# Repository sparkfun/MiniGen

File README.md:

SparkFun MiniGen - Pro Mini Signal Generator Shield
===================================================

[  
*MiniGen Signal Generator (BOB-11420)*](https://www.sparkfun.com/products/11420)

The [MiniGen](https://www.sparkfun.com/products/11420) designed to be used
either as a stand-alone board or as a shield that can be placed on top of an
Arduino Pro Mini. It's capable of generating sine, square or triangle waves at
up to 3MHz, and approximately 1Vp-p. The output is at a DC offset of Vcc/2.
Neither the offset nor the amplitude can be varied.

The MiniGen can be powered by any voltage from 2.3V to 5.5V, so it can be used
with either a 3.3V or 5V Pro Mini without any voltage regulation or signal level
shifting needed.

Repository Contents
-------------------
* **/Hardware** - Eagle design files (.brd, .sch)
* **/Libraries** - Libraries for use with the <PRODUCT NAME>
* **/Production** - Production panel files (.brd)

Documentation
--------------
* **[Library](https://github.com/sparkfun/SparkFun_MiniGen_Arduino_Library)** -  Arduinolibrary for the MiniGen.
* **[Hookup Guide](https://learn.sparkfun.com/tutorials/minigen-hookup-guide)** - Basic hookup guide for the MiniGen.
* **[SparkFun Fritzing repo](https://github.com/sparkfun/Fritzing_Parts)** - Fritzing diagrams for SparkFun products.
* **[SparkFun 3D Model repo](https://github.com/sparkfun/3D_Models)** - 3D models of SparkFun products. 

License Information
-------------------
This product is _**open source**_! 

The **hardware** is released under [Creative Commons ShareAlike 4.0 International](https://creativecommons.org/licenses/by-sa/4.0/).

The **code** is beerware; if you see me (or any other SparkFun employee) at the local, and you've found our code helpful, please buy us a round!

Please use, reuse, and modify these files as you see fit. Please maintain attribution to SparkFun Electronics and release anything derivative under the same license.

Distributed as-is; no warranty is given.

- Your friends at SparkFun.

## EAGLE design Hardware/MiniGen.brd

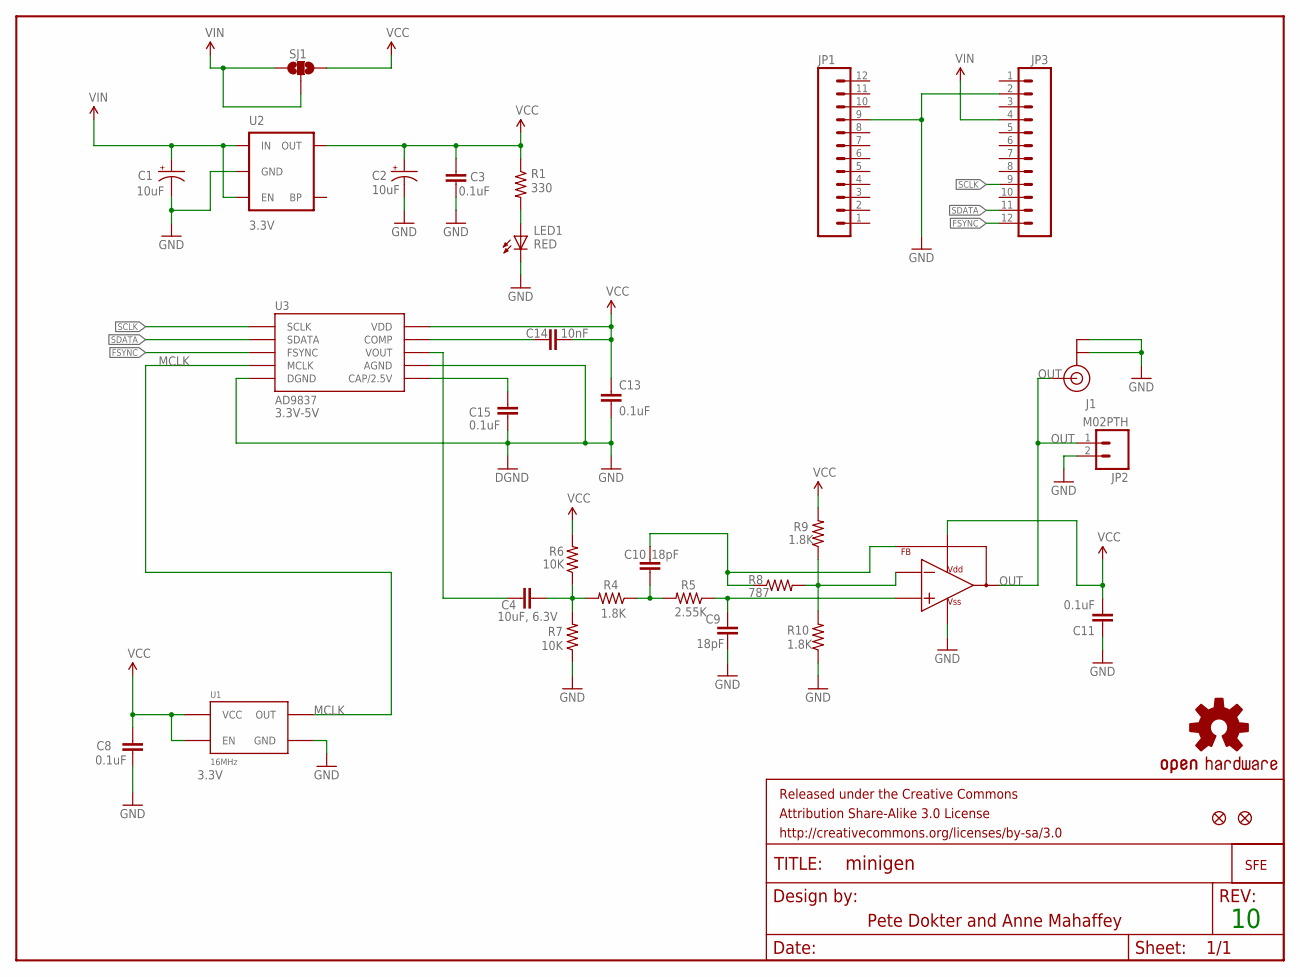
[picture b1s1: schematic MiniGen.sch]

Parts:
C1, C2: 10uF; EIA3528
C3, C8, C11, C13, C15: 0.1uF; 0603-CAP
C4: 10uF, 6.3V; 0603-CAP
C9, C10: 18pF; 0603-CAP
C14: 10nF; 0603-CAP
FID1, FID2: FIDUCIAL1X2; FIDUCIAL-1X2
FRAME1: FRAME-LETTER; CREATIVE_COMMONS
J1: U.FL
JP1, JP3: M12PTH; 1X12
JP2: M02PTH; 1X02
JP4: LOGO-SFENEW; SFE-NEW-WEBLOGO
LED1: RED; LED-0603
R1: 330; 0603-RES
R4, R9, R10: 1.8K; 0603-RES
R5: 2.55K; 0603-RES
R6, R7: 10K; 0603-RES
R8: 787; 0603-RES
SJ1: SOLDERJUMPER_2WAYT; SJ_2
U1: 16MHz; CRYSTAL-SMD-7X5
U2: 3.3V; SOT23-5
U3: AD9837
U4: ADC8045; SO08
U$2: OSHW-LOGOS; OSHW-LOGO-S

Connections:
FSYNC: JP3.12, U3.P$8 (FSYNC)
GND: C1.C (-), C2.C (-), C3.2, C8.2, C9.1, C11.1, C13.2, C15.2, J1.P$1 (GND), J1.P$2 (GND), JP1.9, JP2.2, JP3.2, LED1.C, R7.1, R10.1, U1.P$2 (GND), U2.2 (GND), U3.P$0 (DGND), U3.P$4 (DGND), U3.P$9 (AGND), U4.4 (VSS)
MCLK: U1.P$3 (OUT), U3.P$5 (MCLK)
unnamed: LED1.A, R1.2
unnamed: C9.2, R5.1, U4.3 (IN+)
unnamed: C10.1, R4.1, R5.2
unnamed: C10.2, R8.1, U4.1 (FB)
unnamed: C15.1, U3.P$3 (CAP/2.5V)
unnamed: R8.2, R9.1, R10.2, U4.2 (IN-)
unnamed: C4.2, R4.2, R6.1, R7.2
unnamed: C4.1, U3.P$10 (VOUT)
unnamed: C14.1, U3.P$1 (COMP)
OUT: J1.P$3 (SIGNAL), JP2.1, U4.6 (OUT)
SCLK: JP3.9, U3.P$7 (SCLK)
SDATA: JP3.11, U3.P$6 (SDATA)
VCC: C2.A (+), C3.1, C8.1, C11.2, C13.1, C14.2, R1.1, R6.2, R9.2, SJ1.3, U1.P$1 (EN), U1.P$4 (VCC), U2.5 (OUT), U3.P$2 (VDD), U4.7 (VDD)
VIN: C1.A (+), JP3.4, SJ1.1, SJ1.2, U2.1 (IN), U2.3 (EN)

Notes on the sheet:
Pete Dokter and Anne Mahaffey
3.3V
3.3V-5V

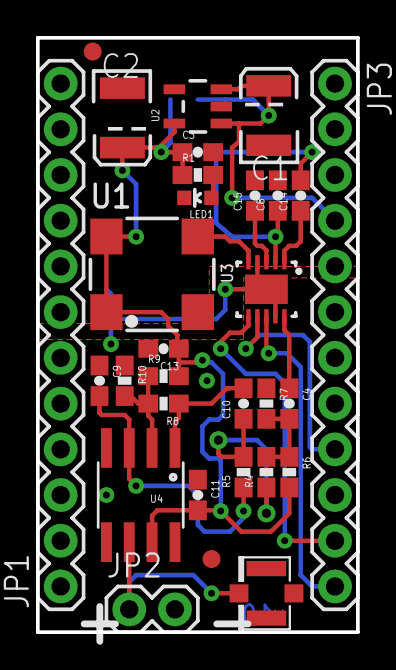
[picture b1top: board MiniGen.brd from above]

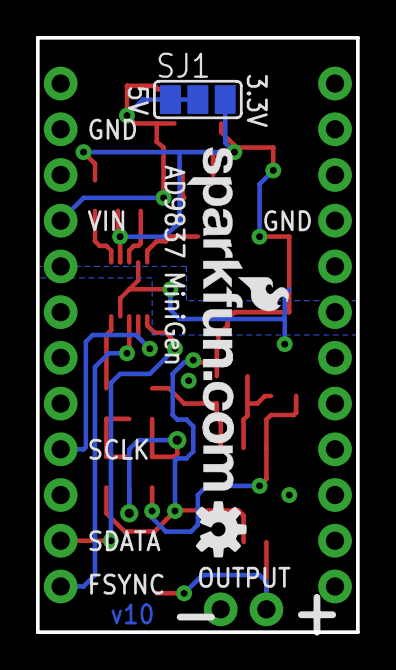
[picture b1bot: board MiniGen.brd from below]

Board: 2 copper layers, 17.8 x 33.0 mm, 34 parts (3 on the bottom side), 17 nets.

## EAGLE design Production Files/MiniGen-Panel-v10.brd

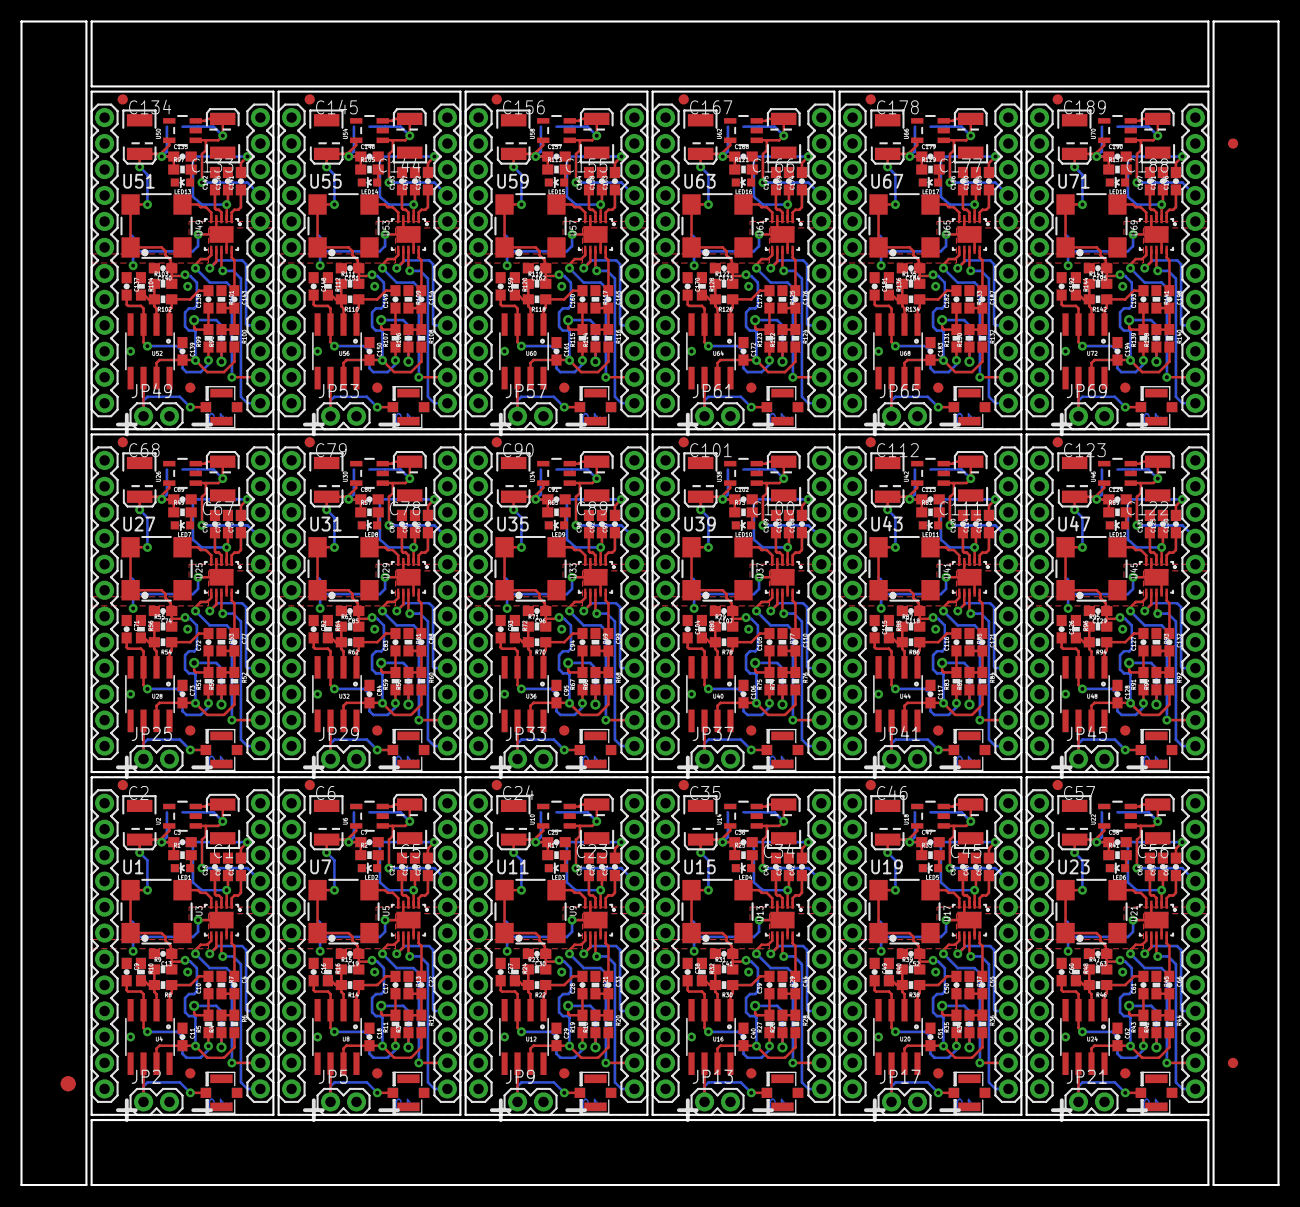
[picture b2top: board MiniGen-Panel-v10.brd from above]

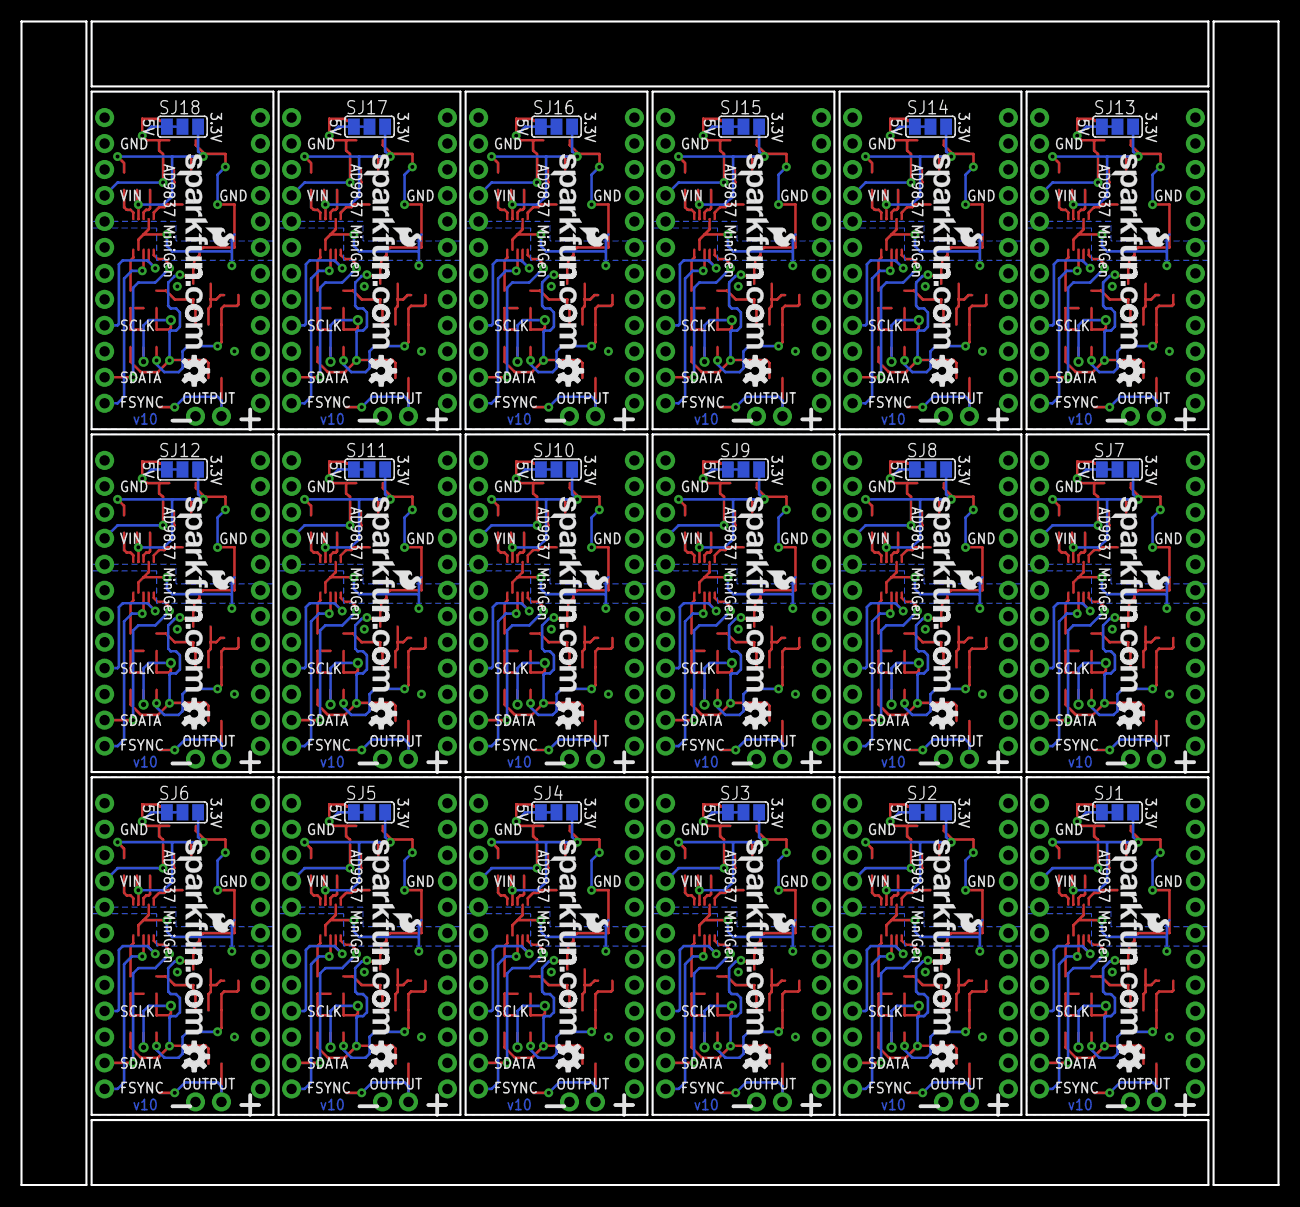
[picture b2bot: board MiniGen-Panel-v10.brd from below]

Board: 2 copper layers, 122.9 x 113.8 mm, 597 parts (54 on the bottom side), 306 nets.

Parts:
C1, C2, C5, C6, C23, C24, C34, C35, C45, C46, C56, C57, C67, C68, C78, C79, C89, C90, C100, C101, C111, C112, C122, C123, C133, C134, C144, C145, C155, C156, C166, C167, C177, C178, C188, C189: 10uF; EIA3528
C3, C7, C8, C11, C12, C13, C15, C18, C19, C21, C25, C26, C29, C30, C32, C36, C37, C40, C41, C43, C47, C48, C51, C52, C54, C58, C59, C62, C63, C65, C69, C70, C73, C74, C76, C80, C81, C84, C85, C87, C91, C92, C95, C96, C98, C102, C103, C106, C107, C109, C113, C114, C117, C118, C120, C124, C125, C128, C129, C131, C135, C136, C139, C140, C142, C146, C147, C150, C151, C153, C157, C158, C161, C162, C164, C168, C169, C172, C173, C175, C179, C180, C183, C184, C186, C190, C191, C194, C195, C197: 0.1uF; 0603-CAP
C4, C22, C33, C44, C55, C66, C77, C88, C99, C110, C121, C132, C143, C154, C165, C176, C187, C198: 10uF, 6.3V; 0603-CAP
C9, C10, C16, C17, C27, C28, C38, C39, C49, C50, C60, C61, C71, C72, C82, C83, C93, C94, C104, C105, C115, C116, C126, C127, C137, C138, C148, C149, C159, C160, C170, C171, C181, C182, C192, C193: 18pF; 0603-CAP
C14, C20, C31, C42, C53, C64, C75, C86, C97, C108, C119, C130, C141, C152, C163, C174, C185, C196: 10nF; 0603-CAP
E$1: FIDUCIAL-1.5X3
E$4, E$6: FIDUCIAL-1X2
FID1, FID2, FID3, FID4, FID5, FID6, FID7, FID8, FID9, FID10, FID11, FID12, FID13, FID14, FID15, FID16, FID17, FID18, FID19, FID20, FID21, FID22, FID23, FID24, FID25, FID26, FID27, FID28, FID29, FID30, FID31, FID32, FID33, FID34, FID35, FID36: FIDUCIAL1X2; FIDUCIAL-1X2
J1, J2, J3, J4, J5, J6, J7, J8, J9, J10, J11, J12, J13, J14, J15, J16, J17, J18: U.FL
JP1, JP3, JP6, JP7, JP10, JP11, JP14, JP15, JP18, JP19, JP22, JP23, JP26, JP27, JP30, JP31, JP34, JP35, JP38, JP39, JP42, JP43, JP46, JP47, JP50, JP51, JP54, JP55, JP58, JP59, JP62, JP63, JP66, JP67, JP70, JP71: M12PTH; 1X12
JP2, JP5, JP9, JP13, JP17, JP21, JP25, JP29, JP33, JP37, JP41, JP45, JP49, JP53, JP57, JP61, JP65, JP69: M02PTH; 1X02
JP4, JP8, JP12, JP16, JP20, JP24, JP28, JP32, JP36, JP40, JP44, JP48, JP52, JP56, JP60, JP64, JP68, JP72: LOGO-SFENEW; SFE-NEW-WEBLOGO
LED1, LED2, LED3, LED4, LED5, LED6, LED7, LED8, LED9, LED10, LED11, LED12, LED13, LED14, LED15, LED16, LED17, LED18: RED; LED-0603
R1, R2, R17, R25, R33, R41, R49, R57, R65, R73, R81, R89, R97, R105, R113, R121, R129, R137: 330; 0603-RES
R3, R4, R9, R10, R15, R16, R18, R23, R24, R26, R31, R32, R34, R39, R40, R42, R47, R48, R50, R55, R56, R58, R63, R64, R66, R71, R72, R74, R79, R80, R82, R87, R88, R90, R95, R96, R98, R103, R104, R106, R111, R112, R114, R119, R120, R122, R127, R128, R130, R135, R136, R138, R143, R144: 1.8K; 0603-RES
R5, R11, R19, R27, R35, R43, R51, R59, R67, R75, R83, R91, R99, R107, R115, R123, R131, R139: 2.55K; 0603-RES
R6, R7, R12, R13, R20, R21, R28, R29, R36, R37, R44, R45, R52, R53, R60, R61, R68, R69, R76, R77, R84, R85, R92, R93, R100, R101, R108, R109, R116, R117, R124, R125, R132, R133, R140, R141: 10K; 0603-RES
R8, R14, R22, R30, R38, R46, R54, R62, R70, R78, R86, R94, R102, R110, R118, R126, R134, R142: 787; 0603-RES
SJ1, SJ2, SJ3, SJ4, SJ5, SJ6, SJ7, SJ8, SJ9, SJ10, SJ11, SJ12, SJ13, SJ14, SJ15, SJ16, SJ17, SJ18: SJ_2
U1, U7, U11, U15, U19, U23, U27, U31, U35, U39, U43, U47, U51, U55, U59, U63, U67, U71: 16MHz; CRYSTAL-SMD-7X5
U2, U6, U10, U14, U18, U22, U26, U30, U34, U38, U42, U46, U50, U54, U58, U62, U66, U70: 3.3V; SOT23-5
U3, U5, U9, U13, U17, U21, U25, U29, U33, U37, U41, U45, U49, U53, U57, U61, U65, U69: AD9837
U4, U8, U12, U16, U20, U24, U28, U32, U36, U40, U44, U48, U52, U56, U60, U64, U68, U72: SO08
U$1, U$2, U$3, U$4, U$5, U$6, U$7, U$8, U$9, U$10, U$11, U$12, U$13, U$14, U$15, U$16, U$17, U$18: OSHW-LOGOS; OSHW-LOGO-S

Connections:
FSYNC: JP3.12, U3.P$8
FSYNC1: JP7.12, U5.P$8
FSYNC2: JP11.12, U9.P$8
FSYNC3: JP15.12, U13.P$8
FSYNC4: JP19.12, U17.P$8
FSYNC5: JP23.12, U21.P$8
FSYNC6: JP27.12, U25.P$8
FSYNC7: JP31.12, U29.P$8
FSYNC8: JP35.12, U33.P$8
FSYNC9: JP39.12, U37.P$8
FSYNC10: JP43.12, U41.P$8
FSYNC11: JP47.12, U45.P$8
FSYNC12: JP51.12, U49.P$8
FSYNC13: JP55.12, U53.P$8
FSYNC14: JP59.12, U57.P$8
FSYNC15: JP63.12, U61.P$8
FSYNC16: JP67.12, U65.P$8
FSYNC17: JP71.12, U69.P$8
GND: C1.C, C2.C, C3.2, C8.2, C9.1, C11.1, C13.2, C15.2, J1.P$1, J1.P$2, JP1.9, JP2.2, JP3.2, LED1.C, R7.1, R10.1, U1.P$2, U2.2, U3.P$0, U3.P$4, U3.P$9, U4.4
GND1: C5.C, C6.C, C7.2, C12.2, C16.1, C18.1, C19.2, C21.2, J2.P$1, J2.P$2, JP5.2, JP6.9, JP7.2, LED2.C, R13.1, R16.1, U5.P$0, U5.P$4, U5.P$9, U6.2, U7.P$2, U8.4
GND2: C23.C, C24.C, C25.2, C26.2, C27.1, C29.1, C30.2, C32.2, J3.P$1, J3.P$2, JP9.2, JP10.9, JP11.2, LED3.C, R21.1, R24.1, U9.P$0, U9.P$4, U9.P$9, U10.2, U11.P$2, U12.4
GND3: C34.C, C35.C, C36.2, C37.2, C38.1, C40.1, C41.2, C43.2, J4.P$1, J4.P$2, JP13.2, JP14.9, JP15.2, LED4.C, R29.1, R32.1, U13.P$0, U13.P$4, U13.P$9, U14.2, U15.P$2, U16.4
GND4: C45.C, C46.C, C47.2, C48.2, C49.1, C51.1, C52.2, C54.2, J5.P$1, J5.P$2, JP17.2, JP18.9, JP19.2, LED5.C, R37.1, R40.1, U17.P$0, U17.P$4, U17.P$9, U18.2, U19.P$2, U20.4
GND5: C56.C, C57.C, C58.2, C59.2, C60.1, C62.1, C63.2, C65.2, J6.P$1, J6.P$2, JP21.2, JP22.9, JP23.2, LED6.C, R45.1, R48.1, U21.P$0, U21.P$4, U21.P$9, U22.2, U23.P$2, U24.4
GND6: C67.C, C68.C, C69.2, C70.2, C71.1, C73.1, C74.2, C76.2, J7.P$1, J7.P$2, JP25.2, JP26.9, JP27.2, LED7.C, R53.1, R56.1, U25.P$0, U25.P$4, U25.P$9, U26.2, U27.P$2, U28.4
GND7: C78.C, C79.C, C80.2, C81.2, C82.1, C84.1, C85.2, C87.2, J8.P$1, J8.P$2, JP29.2, JP30.9, JP31.2, LED8.C, R61.1, R64.1, U29.P$0, U29.P$4, U29.P$9, U30.2, U31.P$2, U32.4
GND8: C89.C, C90.C, C91.2, C92.2, C93.1, C95.1, C96.2, C98.2, J9.P$1, J9.P$2, JP33.2, JP34.9, JP35.2, LED9.C, R69.1, R72.1, U33.P$0, U33.P$4, U33.P$9, U34.2, U35.P$2, U36.4
GND9: C100.C, C101.C, C102.2, C103.2, C104.1, C106.1, C107.2, C109.2, J10.P$1, J10.P$2, JP37.2, JP38.9, JP39.2, LED10.C, R77.1, R80.1, U37.P$0, U37.P$4, U37.P$9, U38.2, U39.P$2, U40.4
GND10: C111.C, C112.C, C113.2, C114.2, C115.1, C117.1, C118.2, C120.2, J11.P$1, J11.P$2, JP41.2, JP42.9, JP43.2, LED11.C, R85.1, R88.1, U41.P$0, U41.P$4, U41.P$9, U42.2, U43.P$2, U44.4
GND11: C122.C, C123.C, C124.2, C125.2, C126.1, C128.1, C129.2, C131.2, J12.P$1, J12.P$2, JP45.2, JP46.9, JP47.2, LED12.C, R93.1, R96.1, U45.P$0, U45.P$4, U45.P$9, U46.2, U47.P$2, U48.4
GND12: C133.C, C134.C, C135.2, C136.2, C137.1, C139.1, C140.2, C142.2, J13.P$1, J13.P$2, JP49.2, JP50.9, JP51.2, LED13.C, R101.1, R104.1, U49.P$0, U49.P$4, U49.P$9, U50.2, U51.P$2, U52.4
GND13: C144.C, C145.C, C146.2, C147.2, C148.1, C150.1, C151.2, C153.2, J14.P$1, J14.P$2, JP53.2, JP54.9, JP55.2, LED14.C, R109.1, R112.1, U53.P$0, U53.P$4, U53.P$9, U54.2, U55.P$2, U56.4
GND14: C155.C, C156.C, C157.2, C158.2, C159.1, C161.1, C162.2, C164.2, J15.P$1, J15.P$2, JP57.2, JP58.9, JP59.2, LED15.C, R117.1, R120.1, U57.P$0, U57.P$4, U57.P$9, U58.2, U59.P$2, U60.4
GND15: C166.C, C167.C, C168.2, C169.2, C170.1, C172.1, C173.2, C175.2, J16.P$1, J16.P$2, JP61.2, JP62.9, JP63.2, LED16.C, R125.1, R128.1, U61.P$0, U61.P$4, U61.P$9, U62.2, U63.P$2, U64.4
GND16: C177.C, C178.C, C179.2, C180.2, C181.1, C183.1, C184.2, C186.2, J17.P$1, J17.P$2, JP65.2, JP66.9, JP67.2, LED17.C, R133.1, R136.1, U65.P$0, U65.P$4, U65.P$9, U66.2, U67.P$2, U68.4
GND17: C188.C, C189.C, C190.2, C191.2, C192.1, C194.1, C195.2, C197.2, J18.P$1, J18.P$2, JP69.2, JP70.9, JP71.2, LED18.C, R141.1, R144.1, U69.P$0, U69.P$4, U69.P$9, U70.2, U71.P$2, U72.4
MCLK: U1.P$3, U3.P$5
MCLK1: U5.P$5, U7.P$3
MCLK2: U9.P$5, U11.P$3
MCLK3: U13.P$5, U15.P$3
MCLK4: U17.P$5, U19.P$3
MCLK5: U21.P$5, U23.P$3
MCLK6: U25.P$5, U27.P$3
MCLK7: U29.P$5, U31.P$3
MCLK8: U33.P$5, U35.P$3
MCLK9: U37.P$5, U39.P$3
MCLK10: U41.P$5, U43.P$3
MCLK11: U45.P$5, U47.P$3
MCLK12: U49.P$5, U51.P$3
MCLK13: U53.P$5, U55.P$3
MCLK14: U57.P$5, U59.P$3
MCLK15: U61.P$5, U63.P$3
MCLK16: U65.P$5, U67.P$3
MCLK17: U69.P$5, U71.P$3
unnamed: LED2.A, R2.2
unnamed: C22.2, R3.2, R12.1, R13.2
unnamed: LED1.A, R1.2
unnamed: C22.1, U5.P$10
unnamed: C20.1, U5.P$1
unnamed: C21.1, U5.P$3
unnamed: C9.2, R5.1, U4.3
unnamed: C10.1, R4.1, R5.2
unnamed: C10.2, R8.1, U4.1
unnamed: C15.1, U3.P$3
unnamed: C16.2, R11.1, U8.3
unnamed: R8.2, R9.1, R10.2, U4.2
unnamed: C17.1, R3.1, R11.2
unnamed: C4.2, R4.2, R6.1, R7.2
unnamed: R14.2, R15.1, R16.2, U8.2
unnamed: C17.2, R14.1, U8.1
unnamed: LED3.A, R17.2
unnamed: C33.2, R18.2, R20.1, R21.2
unnamed: C33.1, U9.P$10
unnamed: C31.1, U9.P$1
unnamed: C4.1, U3.P$10
unnamed: C32.1, U9.P$3
unnamed: C14.1, U3.P$1
unnamed: C27.2, R19.1, U12.3
unnamed: C28.1, R18.1, R19.2
unnamed: R22.2, R23.1, R24.2, U12.2
unnamed: C28.2, R22.1, U12.1
unnamed: LED4.A, R25.2
unnamed: C44.2, R26.2, R28.1, R29.2
unnamed: C44.1, U13.P$10
unnamed: C42.1, U13.P$1
unnamed: C43.1, U13.P$3
unnamed: C38.2, R27.1, U16.3
unnamed: C39.1, R26.1, R27.2
unnamed: R30.2, R31.1, R32.2, U16.2
unnamed: C39.2, R30.1, U16.1
unnamed: LED5.A, R33.2
unnamed: C55.2, R34.2, R36.1, R37.2
unnamed: C55.1, U17.P$10
unnamed: C53.1, U17.P$1
unnamed: C54.1, U17.P$3
unnamed: C49.2, R35.1, U20.3
unnamed: C50.1, R34.1, R35.2
unnamed: R38.2, R39.1, R40.2, U20.2
unnamed: C50.2, R38.1, U20.1
unnamed: LED6.A, R41.2
unnamed: C66.2, R42.2, R44.1, R45.2
unnamed: C66.1, U21.P$10
unnamed: C64.1, U21.P$1
unnamed: C65.1, U21.P$3
unnamed: C60.2, R43.1, U24.3
unnamed: C61.1, R42.1, R43.2
unnamed: R46.2, R47.1, R48.2, U24.2
unnamed: C61.2, R46.1, U24.1
unnamed: LED7.A, R49.2
unnamed: C77.2, R50.2, R52.1, R53.2
unnamed: C77.1, U25.P$10
unnamed: C75.1, U25.P$1
unnamed: C76.1, U25.P$3
unnamed: C71.2, R51.1, U28.3
unnamed: C72.1, R50.1, R51.2
unnamed: R54.2, R55.1, R56.2, U28.2
unnamed: C72.2, R54.1, U28.1
unnamed: LED8.A, R57.2
unnamed: C88.2, R58.2, R60.1, R61.2
unnamed: C88.1, U29.P$10
unnamed: C86.1, U29.P$1
unnamed: C87.1, U29.P$3
unnamed: C82.2, R59.1, U32.3
unnamed: C83.1, R58.1, R59.2
unnamed: R62.2, R63.1, R64.2, U32.2
unnamed: C83.2, R62.1, U32.1
unnamed: LED9.A, R65.2
unnamed: C99.2, R66.2, R68.1, R69.2
unnamed: C99.1, U33.P$10
unnamed: C97.1, U33.P$1
unnamed: C98.1, U33.P$3
unnamed: C93.2, R67.1, U36.3
unnamed: C94.1, R66.1, R67.2
unnamed: R70.2, R71.1, R72.2, U36.2
unnamed: C94.2, R70.1, U36.1
unnamed: LED10.A, R73.2
unnamed: C110.2, R74.2, R76.1, R77.2
unnamed: C110.1, U37.P$10
unnamed: C108.1, U37.P$1
unnamed: C109.1, U37.P$3
unnamed: C104.2, R75.1, U40.3
unnamed: C105.1, R74.1, R75.2
unnamed: R78.2, R79.1, R80.2, U40.2
unnamed: C105.2, R78.1, U40.1
unnamed: LED11.A, R81.2
unnamed: C121.2, R82.2, R84.1, R85.2
unnamed: C121.1, U41.P$10
unnamed: C119.1, U41.P$1
unnamed: C120.1, U41.P$3
unnamed: C115.2, R83.1, U44.3
unnamed: C116.1, R82.1, R83.2
unnamed: R86.2, R87.1, R88.2, U44.2
unnamed: C116.2, R86.1, U44.1
unnamed: LED12.A, R89.2
unnamed: C132.2, R90.2, R92.1, R93.2
unnamed: C132.1, U45.P$10
unnamed: C130.1, U45.P$1
unnamed: C131.1, U45.P$3
unnamed: C126.2, R91.1, U48.3
unnamed: C127.1, R90.1, R91.2
unnamed: R94.2, R95.1, R96.2, U48.2
unnamed: C127.2, R94.1, U48.1
unnamed: LED13.A, R97.2
unnamed: C143.2, R98.2, R100.1, R101.2
unnamed: C143.1, U49.P$10
unnamed: C141.1, U49.P$1
unnamed: C142.1, U49.P$3
unnamed: C137.2, R99.1, U52.3
unnamed: C138.1, R98.1, R99.2
unnamed: R102.2, R103.1, R104.2, U52.2
unnamed: C138.2, R102.1, U52.1
unnamed: LED14.A, R105.2
unnamed: C154.2, R106.2, R108.1, R109.2
unnamed: C154.1, U53.P$10
unnamed: C152.1, U53.P$1
unnamed: C153.1, U53.P$3
unnamed: C148.2, R107.1, U56.3
unnamed: C149.1, R106.1, R107.2
unnamed: R110.2, R111.1, R112.2, U56.2
unnamed: C149.2, R110.1, U56.1
unnamed: LED15.A, R113.2
unnamed: C165.2, R114.2, R116.1, R117.2
unnamed: C165.1, U57.P$10
unnamed: C163.1, U57.P$1
unnamed: C164.1, U57.P$3
unnamed: C159.2, R115.1, U60.3
unnamed: C160.1, R114.1, R115.2
unnamed: R118.2, R119.1, R120.2, U60.2
unnamed: C160.2, R118.1, U60.1
unnamed: LED16.A, R121.2
unnamed: C176.2, R122.2, R124.1, R125.2
unnamed: C176.1, U61.P$10
unnamed: C174.1, U61.P$1
unnamed: C175.1, U61.P$3
unnamed: C170.2, R123.1, U64.3
unnamed: C171.1, R122.1, R123.2
unnamed: R126.2, R127.1, R128.2, U64.2
unnamed: C171.2, R126.1, U64.1
unnamed: LED17.A, R129.2
unnamed: C187.2, R130.2, R132.1, R133.2
unnamed: C187.1, U65.P$10
unnamed: C185.1, U65.P$1
unnamed: C186.1, U65.P$3
unnamed: C181.2, R131.1, U68.3
unnamed: C182.1, R130.1, R131.2
unnamed: R134.2, R135.1, R136.2, U68.2
unnamed: C182.2, R134.1, U68.1
unnamed: LED18.A, R137.2
unnamed: C198.2, R138.2, R140.1, R141.2
unnamed: C198.1, U69.P$10
unnamed: C196.1, U69.P$1
unnamed: C197.1, U69.P$3
unnamed: C192.2, R139.1, U72.3
unnamed: C193.1, R138.1, R139.2
unnamed: R142.2, R143.1, R144.2, U72.2
unnamed: C193.2, R142.1, U72.1
OUT: J1.P$3, JP2.1, U4.6
OUT1: J2.P$3, JP5.1, U8.6
OUT2: J3.P$3, JP9.1, U12.6
OUT3: J4.P$3, JP13.1, U16.6
OUT4: J5.P$3, JP17.1, U20.6
OUT5: J6.P$3, JP21.1, U24.6
OUT6: J7.P$3, JP25.1, U28.6
OUT7: J8.P$3, JP29.1, U32.6
OUT8: J9.P$3, JP33.1, U36.6
OUT9: J10.P$3, JP37.1, U40.6
OUT10: J11.P$3, JP41.1, U44.6
OUT11: J12.P$3, JP45.1, U48.6
OUT12: J13.P$3, JP49.1, U52.6
OUT13: J14.P$3, JP53.1, U56.6
OUT14: J15.P$3, JP57.1, U60.6
OUT15: J16.P$3, JP61.1, U64.6
OUT16: J17.P$3, JP65.1, U68.6
OUT17: J18.P$3, JP69.1, U72.6
SCLK: JP3.9, U3.P$7
SCLK1: JP7.9, U5.P$7
SCLK2: JP11.9, U9.P$7
SCLK3: JP15.9, U13.P$7
SCLK4: JP19.9, U17.P$7
SCLK5: JP23.9, U21.P$7
SCLK6: JP27.9, U25.P$7
SCLK7: JP31.9, U29.P$7
SCLK8: JP35.9, U33.P$7
SCLK9: JP39.9, U37.P$7
SCLK10: JP43.9, U41.P$7
SCLK11: JP47.9, U45.P$7
SCLK12: JP51.9, U49.P$7
SCLK13: JP55.9, U53.P$7
SCLK14: JP59.9, U57.P$7
SCLK15: JP63.9, U61.P$7
SCLK16: JP67.9, U65.P$7
SCLK17: JP71.9, U69.P$7
SDATA: JP3.11, U3.P$6
SDATA1: JP7.11, U5.P$6
SDATA2: JP11.11, U9.P$6
SDATA3: JP15.11, U13.P$6
SDATA4: JP19.11, U17.P$6
SDATA5: JP23.11, U21.P$6
SDATA6: JP27.11, U25.P$6
SDATA7: JP31.11, U29.P$6
SDATA8: JP35.11, U33.P$6
SDATA9: JP39.11, U37.P$6
SDATA10: JP43.11, U41.P$6
SDATA11: JP47.11, U45.P$6
SDATA12: JP51.11, U49.P$6
SDATA13: JP55.11, U53.P$6
SDATA14: JP59.11, U57.P$6
SDATA15: JP63.11, U61.P$6
SDATA16: JP67.11, U65.P$6
SDATA17: JP71.11, U69.P$6
VCC: C2.A, C3.1, C8.1, C11.2, C13.1, C14.2, R1.1, R6.2, R9.2, SJ1.3, U1.P$1, U1.P$4, U2.5, U3.P$2, U4.7
VCC1: C6.A, C7.1, C12.1, C18.2, C19.1, C20.2, R2.1, R12.2, R15.2, SJ2.3, U5.P$2, U6.5, U7.P$1, U7.P$4, U8.7
VCC2: C24.A, C25.1, C26.1, C29.2, C30.1, C31.2, R17.1, R20.2, R23.2, SJ3.3, U9.P$2, U10.5, U11.P$1, U11.P$4, U12.7
VCC3: C35.A, C36.1, C37.1, C40.2, C41.1, C42.2, R25.1, R28.2, R31.2, SJ4.3, U13.P$2, U14.5, U15.P$1, U15.P$4, U16.7
VCC4: C46.A, C47.1, C48.1, C51.2, C52.1, C53.2, R33.1, R36.2, R39.2, SJ5.3, U17.P$2, U18.5, U19.P$1, U19.P$4, U20.7
VCC5: C57.A, C58.1, C59.1, C62.2, C63.1, C64.2, R41.1, R44.2, R47.2, SJ6.3, U21.P$2, U22.5, U23.P$1, U23.P$4, U24.7
VCC6: C68.A, C69.1, C70.1, C73.2, C74.1, C75.2, R49.1, R52.2, R55.2, SJ7.3, U25.P$2, U26.5, U27.P$1, U27.P$4, U28.7
VCC7: C79.A, C80.1, C81.1, C84.2, C85.1, C86.2, R57.1, R60.2, R63.2, SJ8.3, U29.P$2, U30.5, U31.P$1, U31.P$4, U32.7
VCC8: C90.A, C91.1, C92.1, C95.2, C96.1, C97.2, R65.1, R68.2, R71.2, SJ9.3, U33.P$2, U34.5, U35.P$1, U35.P$4, U36.7
VCC9: C101.A, C102.1, C103.1, C106.2, C107.1, C108.2, R73.1, R76.2, R79.2, SJ10.3, U37.P$2, U38.5, U39.P$1, U39.P$4, U40.7
VCC10: C112.A, C113.1, C114.1, C117.2, C118.1, C119.2, R81.1, R84.2, R87.2, SJ11.3, U41.P$2, U42.5, U43.P$1, U43.P$4, U44.7
VCC11: C123.A, C124.1, C125.1, C128.2, C129.1, C130.2, R89.1, R92.2, R95.2, SJ12.3, U45.P$2, U46.5, U47.P$1, U47.P$4, U48.7
VCC12: C134.A, C135.1, C136.1, C139.2, C140.1, C141.2, R97.1, R100.2, R103.2, SJ13.3, U49.P$2, U50.5, U51.P$1, U51.P$4, U52.7
VCC13: C145.A, C146.1, C147.1, C150.2, C151.1, C152.2, R105.1, R108.2, R111.2, SJ14.3, U53.P$2, U54.5, U55.P$1, U55.P$4, U56.7
VCC14: C156.A, C157.1, C158.1, C161.2, C162.1, C163.2, R113.1, R116.2, R119.2, SJ15.3, U57.P$2, U58.5, U59.P$1, U59.P$4, U60.7
VCC15: C167.A, C168.1, C169.1, C172.2, C173.1, C174.2, R121.1, R124.2, R127.2, SJ16.3, U61.P$2, U62.5, U63.P$1, U63.P$4, U64.7
VCC16: C178.A, C179.1, C180.1, C183.2, C184.1, C185.2, R129.1, R132.2, R135.2, SJ17.3, U65.P$2, U66.5, U67.P$1, U67.P$4, U68.7
VCC17: C189.A, C190.1, C191.1, C194.2, C195.1, C196.2, R137.1, R140.2, R143.2, SJ18.3, U69.P$2, U70.5, U71.P$1, U71.P$4, U72.7
VIN: C1.A, JP3.4, SJ1.1, SJ1.2, U2.1, U2.3
VIN1: C5.A, JP7.4, SJ2.1, SJ2.2, U6.1, U6.3
VIN2: C23.A, JP11.4, SJ3.1, SJ3.2, U10.1, U10.3
VIN3: C34.A, JP15.4, SJ4.1, SJ4.2, U14.1, U14.3
VIN4: C45.A, JP19.4, SJ5.1, SJ5.2, U18.1, U18.3
VIN5: C56.A, JP23.4, SJ6.1, SJ6.2, U22.1, U22.3
VIN6: C67.A, JP27.4, SJ7.1, SJ7.2, U26.1, U26.3
VIN7: C78.A, JP31.4, SJ8.1, SJ8.2, U30.1, U30.3
VIN8: C89.A, JP35.4, SJ9.1, SJ9.2, U34.1, U34.3
VIN9: C100.A, JP39.4, SJ10.1, SJ10.2, U38.1, U38.3
VIN10: C111.A, JP43.4, SJ11.1, SJ11.2, U42.1, U42.3
VIN11: C122.A, JP47.4, SJ12.1, SJ12.2, U46.1, U46.3
VIN12: C133.A, JP51.4, SJ13.1, SJ13.2, U50.1, U50.3
VIN13: C144.A, JP55.4, SJ14.1, SJ14.2, U54.1, U54.3
VIN14: C155.A, JP59.4, SJ15.1, SJ15.2, U58.1, U58.3
VIN15: C166.A, JP63.4, SJ16.1, SJ16.2, U62.1, U62.3
VIN16: C177.A, JP67.4, SJ17.1, SJ17.2, U66.1, U66.3
VIN17: C188.A, JP71.4, SJ18.1, SJ18.2, U70.1, U70.3

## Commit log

2014-01-21 Initial file commit
2014-01-22 Added version info.
2014-02-07 Update lib to default to pin 10 for CS
2014-02-07 Advance design to v10 for release.
2014-02-10 Fix labeling on schematic
2014-02-11 Add/modify some silk for release.
2014-02-11 added fiducials
2014-02-11 created panel v10
2014-05-06 Added comments to example sketch
2014-05-06 Edited readme
2014-05-22 Update README.md
    Adding product photo.
2014-05-22 Line ending changes
2015-05-15 Fixing directory structure, naming conventions
2015-05-15 Squashed 'Libraries/Arduino/' content from commit 7212493
    git-subtree-dir: Libraries/Arduino
    git-subtree-split: 7212493b946ac81a992486eb619213eb8305324d

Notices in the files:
parts and their libraries:
SparkFun-AnalogIC: Licensing: CC v3.0 Share-Alike You are welcome to use this library for commercial purposes.
SparkFun-Aesthetics: Released under the Creative Commons Attribution Share-Alike 3.0 License
SparkFun-Aesthetics: http://creativecommons.org/licenses/by-sa/3.0
